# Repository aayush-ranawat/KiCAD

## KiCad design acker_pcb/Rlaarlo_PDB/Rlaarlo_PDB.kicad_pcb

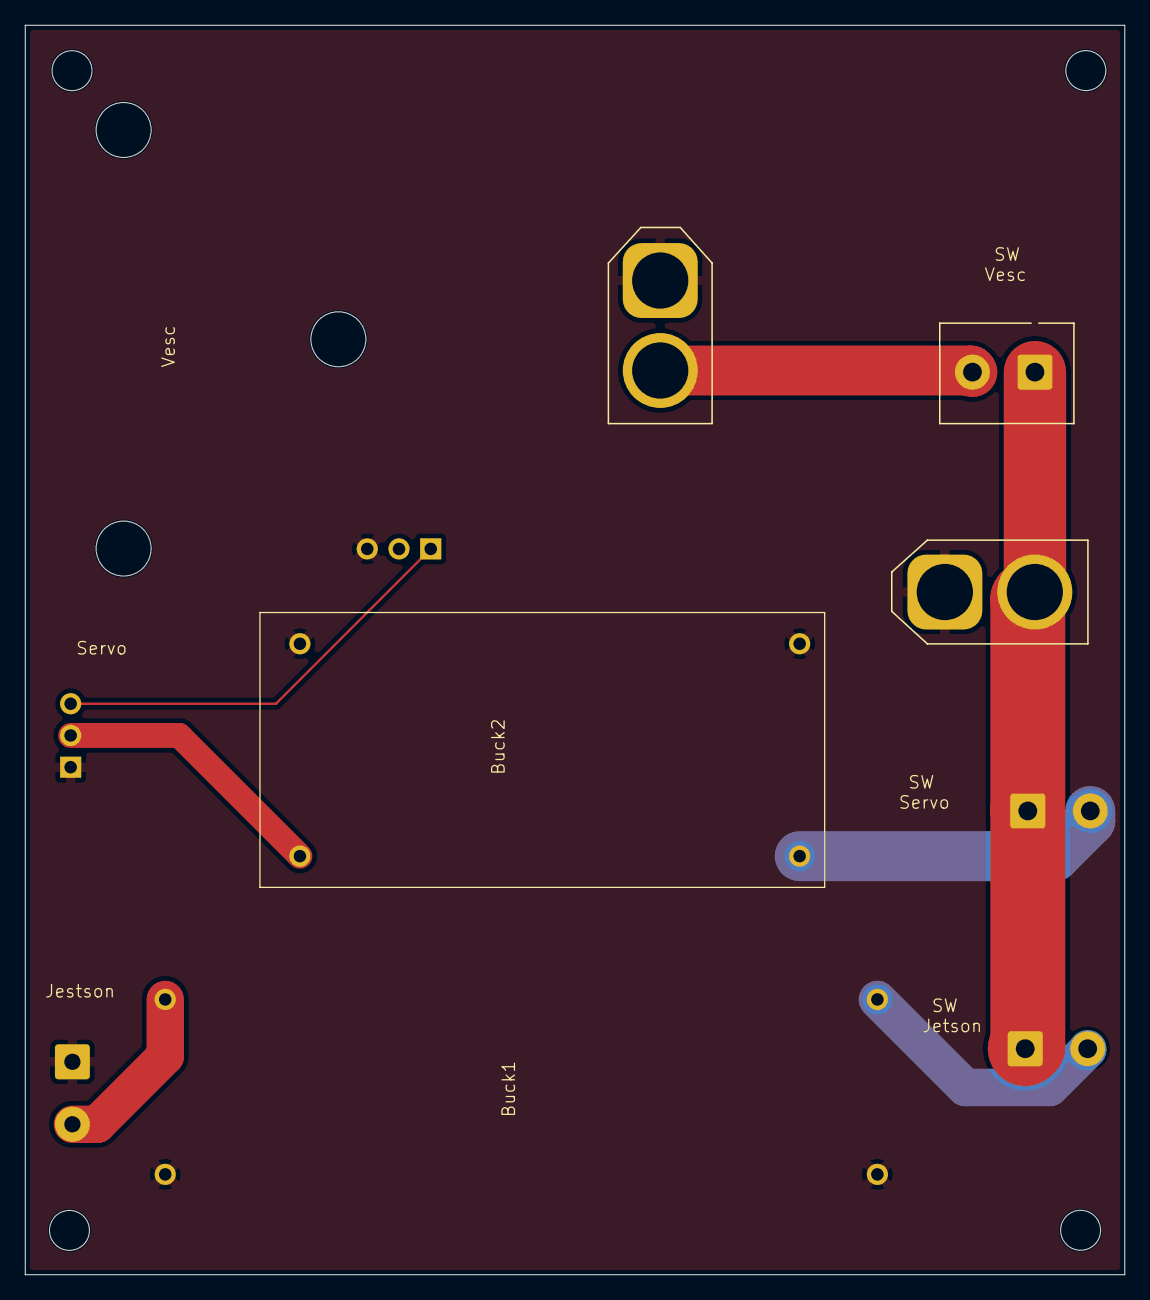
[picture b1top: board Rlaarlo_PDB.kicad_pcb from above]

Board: 2 copper layers, 88.0 x 100.0 mm, 9 parts (0 on the bottom side), 8 nets.

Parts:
Buck1: xl4016; XL4016 BUCK
Buck2: xl4015; XL4015 Buck
J1: xt 60; AMASS_XT60-M_1x02_P7.20mm_Vertical
J2: Conn_01x03_Pin; PinHeader_1x03_P2.54mm_Horizontal
SW: SW_SPST_esb; spst_switch
SW2, SW3: SW_SPST; spst_switch
jetson v: Conn_01x02_Pin; TerminalBlock_MaiXu_MX126-5.0-02P_1x02_P5.00mm
vesc1: vesc

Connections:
+15V: J1.2, SW.1 (A), SW2.1 (A), SW3.1 (A)
GND: Buck1.2 (v_in_-), Buck1.4 (v_out_-), Buck2.2 (v_in_-), Buck2.4 (v_out_-), J1.1, J2.1, jetson v.1, vesc1.1 (v-), vesc1.3 (servo-)
unnamed: Buck1.1 (v_in_+), SW3.2 (B)
unnamed: Buck1.3 (v_out_+), jetson v.2
unnamed: Buck2.1 (v_in_+), SW2.2 (B)
unnamed: Buck2.3 (v_out_+), J2.2
unnamed: J2.3, vesc1.5 (pwm)
unnamed: SW.2 (B), vesc1.2 (v+)

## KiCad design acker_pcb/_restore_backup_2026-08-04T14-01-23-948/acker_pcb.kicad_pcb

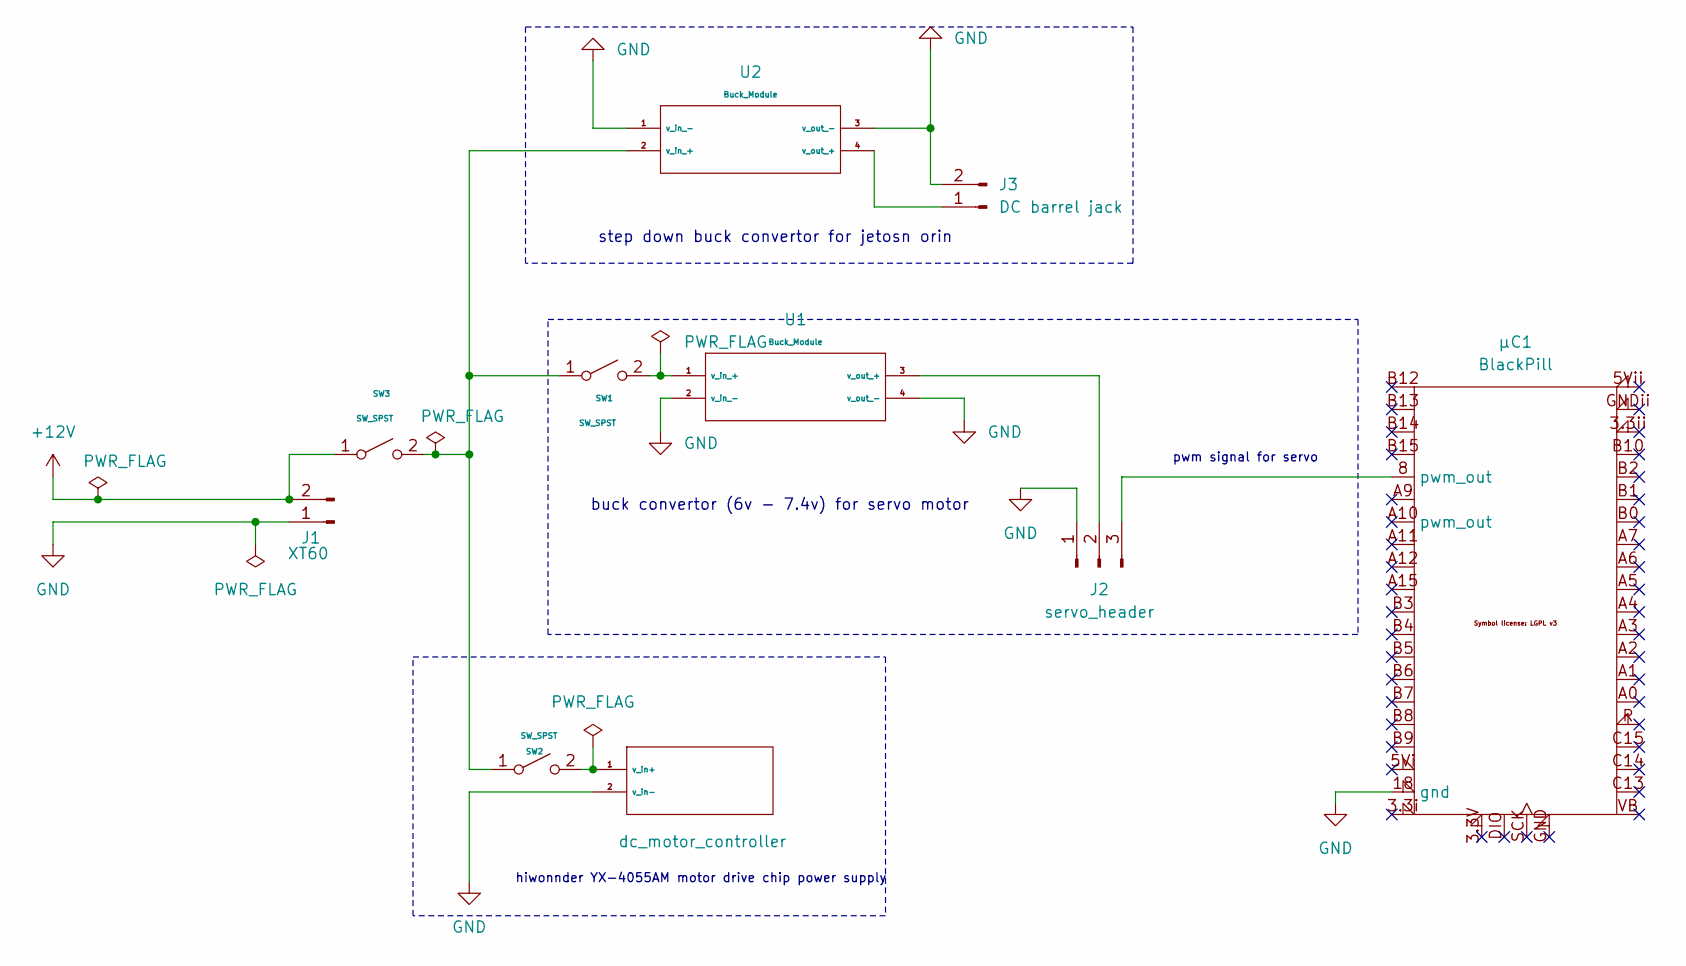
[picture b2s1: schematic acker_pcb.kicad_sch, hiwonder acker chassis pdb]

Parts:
J1: XT60; AMASS_XT60PW-M_1x02_P7.20mm_Horizontal
J2: servo_header; PinHeader_1x03_P2.54mm_Vertical
J3: DC barrel jack; TerminalBlock_MaiXu_MX126-5.0-02P_1x02_P5.00mm
SW1, SW2, SW3: SW_SPST; spst_switch
U1: Buck_Module; XL4015 Buck
U2: Buck_Module; XL4016 BUCK
U3: dc_motor_controller; YX-4055AM motor drive chip
μC1: BlackPill; blackpill

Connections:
+12V: J1.2 (bat_-), SW3.1 (A)
GND: J1.1 (batt_+), J2.1 (servo_gnd), J3.2, U1.2 (v_in_-), U1.4 (v_out_-), U2.1 (v_in_-), U2.3 (v_out_-), U3.2 (v_in-), μC1.18 (gnd)
unnamed: J2.2 (servo_power), U1.3 (v_out_+)
unnamed: J2.3 (signal), μC1.8 (pwm_out)
unnamed: J3.1, U2.4 (v_out_+)
unnamed: SW1.1 (A), SW2.1 (A), SW3.2 (B), U2.2 (v_in_+)
unnamed: SW1.2 (B), U1.1 (v_in_+)
unnamed: SW2.2 (B), U3.1 (v_in+)

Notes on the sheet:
buck convertor (6v - 7.4v) for servo motor
step down buck convertor for jetosn orin
hiwonnder YX-4055AM motor drive chip power supply
pwm signal for servo

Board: 2 copper layers, 10 parts (0 on the bottom side), 8 nets, no tracks yet.

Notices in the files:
acker_pcb/_restore_backup_2026-07-27T09-49-31-600/acker_pcb.kicad_sch:
Symbol license: LGPL v3
